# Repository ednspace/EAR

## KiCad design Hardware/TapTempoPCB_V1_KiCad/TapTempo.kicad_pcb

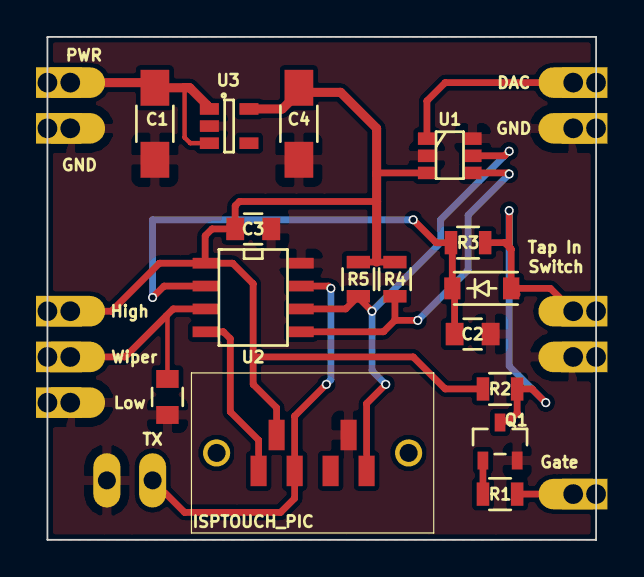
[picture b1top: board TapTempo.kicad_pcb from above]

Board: 2 copper layers, 30.5 x 27.9 mm, 27 parts (0 on the bottom side), 13 nets.

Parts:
C1, C4: 1uF; C_1206_HandSoldering
C2, C3, C5: .1uF; C_0805
D1: DIODE; SOD-123
J1: ISPTOUCH_PIC; ICSP_TOUCH_AVX_9188_6-WAY_MATING_GUIDE
P1: PWR; Castellation
P2, P11: GND; Castellation
P3: CONN_01X02; PINHEAD1-2
P4: DAC; Castellation
P5: Gate; Castellation
P6: Switch_1; Castellation
P7: Switch_2; Castellation
P8: High; Castellation
P9: Wiper; Castellation
P10: Low; Castellation
Q1: 2N3904; sot23
R1: 10K; R_0805
R2: 100K; R_0805
R3, R4, R5: 4.7K; R_0805
U1: MCP4725; SOT-23-6
U2: PIC12F1822; SOIC-8-W
U3: LDK220; SOT-23-5

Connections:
GND: C1.1, C2.2, C3.2, C4.1, C5.2, J1.6, P2.1, P3.1, P7.1, P10.1, P11.1, Q1.2, U1.2, U1.6, U2.8, U3.2
Gatein: P5.1, R1.1
MCLR: J1.1, U2.4
unnamed: C1.2, P1.1, U3.1, U3.3
unnamed: D1.1, P6.1, Q1.3, R2.2, R3.1
unnamed: P4.1, U1.1
unnamed: Q1.1, R1.2
PGC: J1.5, R5.1, U1.5, U2.6
PGD: J1.3, P3.2, U2.7
POT: C5.1, P9.1, U2.3
SDA: R4.2, U1.4, U2.5
TAP: C2.1, D1.2, R3.2, U2.2
VCC: C3.1, C4.2, J1.2, P8.1, R2.1, R4.1, R5.2, U1.3, U2.1, U3.5

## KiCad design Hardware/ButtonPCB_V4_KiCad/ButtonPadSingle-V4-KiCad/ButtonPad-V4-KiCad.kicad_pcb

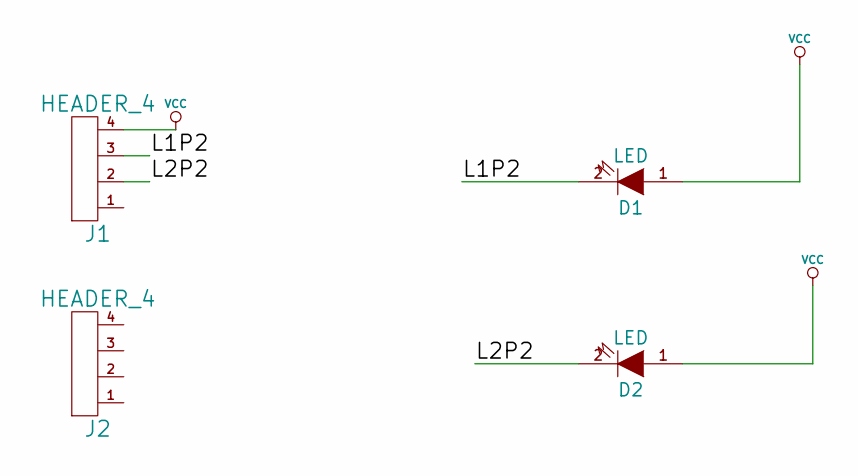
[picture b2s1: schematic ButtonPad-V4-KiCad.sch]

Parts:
D1, D2: LED
J1, J2: HEADER_4

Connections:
/L1P2: D1.2 (K), J1.3
/L2P2: D2.2 (K), J1.2
VCC: D1.1 (A), D2.1 (A), J1.4

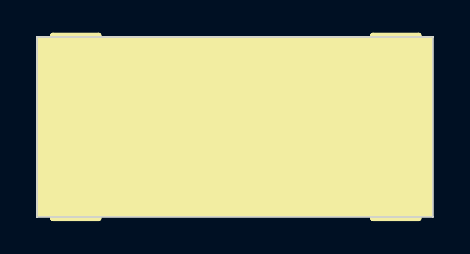
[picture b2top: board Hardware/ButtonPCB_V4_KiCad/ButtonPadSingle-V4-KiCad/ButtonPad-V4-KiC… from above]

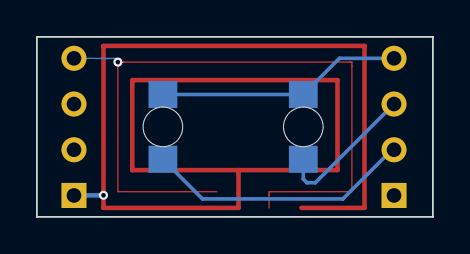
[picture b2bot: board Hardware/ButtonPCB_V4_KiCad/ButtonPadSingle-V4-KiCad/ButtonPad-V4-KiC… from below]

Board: 2 copper layers, 22.0 x 10.0 mm, 4 parts (2 on the bottom side), 3 nets.

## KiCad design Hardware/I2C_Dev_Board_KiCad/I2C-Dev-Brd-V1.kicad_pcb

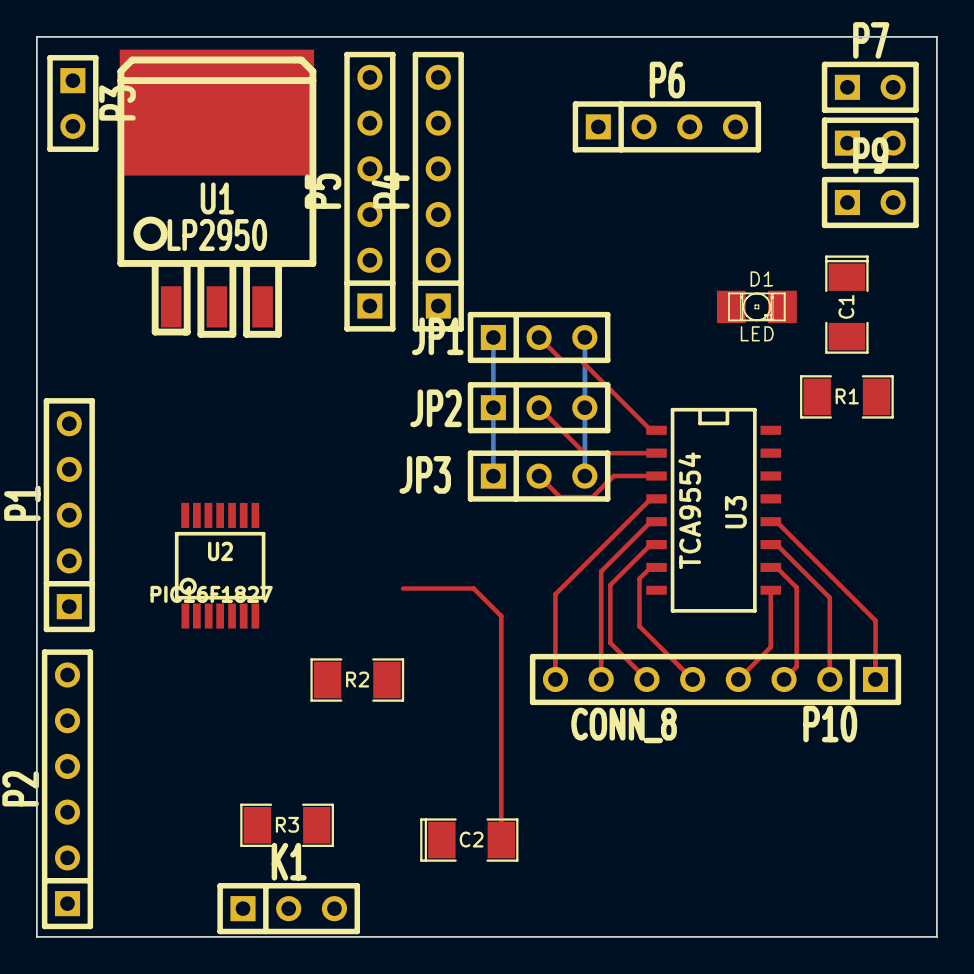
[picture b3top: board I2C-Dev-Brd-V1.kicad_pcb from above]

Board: 2 copper layers, 50.0 x 50.0 mm, 23 parts (0 on the bottom side), 26 nets.

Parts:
C1: 1uF; SM1206POL
C2: 4.7uF; SM1206POL
D1: LED; LED-1206
JP1, JP2, JP3: JUMPER3; SIL-3
K1: POTS; SIL-3
P1: PICKIT2; SIL-5
P2: FTDI SERIAL; SIL-6
P3, P7, P8, P9: CONN_2; SIL-2
P4, P5: CONN_6; SIL-6
P6: CONN_4; SIL-4
P10: CONN_8; SIL-8
R1: 330; SM1206
R2, R3: 4.7K; SM1206
U1: LP2950; TO263
U2: PIC16F1827; SSOP14
U3: TCA9554; SO16N

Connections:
+3.3V: C2.1, JP1.3, JP2.3, JP3.3, P4.1, P4.2, P4.3, P4.4, P4.5, P4.6, R2.1, R3.1, U1.1, U2.14, U3.16
/A0: JP1.2, U3.1
/A1: JP2.2, U3.2
/A2: JP3.2, U3.3
/BLINK: R1.1, U2.9
/I2C_CLK: P8.1, P9.1, R2.2, U2.10, U3.14
/I2C_DAT: P7.2, P8.2, P9.2, R3.2, U2.7, U3.15
/MCLR: P1.5, U2.4
/P0: P10.8, U3.4
/P1: P10.7, U3.5
/P2: P10.6, U3.6
/P3: P10.5, U3.7
/P4: P10.4, U3.9
/P5: P10.3, U3.10
/P6: P10.2, U3.11
/P7: P10.1, U3.12
/PGC: P1.1, U2.12
/PGD: P1.2, U2.13
/RXD: P2.5, U2.11
/TXD: P2.4, U2.8
GND: C1.2, C2.2, D1.2, JP1.1, JP2.1, JP3.1, P1.3, P2.1, P3.1, P5.1, P5.2, P5.3, P5.4, P5.5, P5.6, U1.2, U2.5, U3.8
unnamed: K1.3, U2.1
unnamed: K1.2, U2.2
unnamed: D1.1, R1.2
unnamed: K1.1, U2.3
VDD: C1.1, P1.4, P2.3, P3.2, U1.3

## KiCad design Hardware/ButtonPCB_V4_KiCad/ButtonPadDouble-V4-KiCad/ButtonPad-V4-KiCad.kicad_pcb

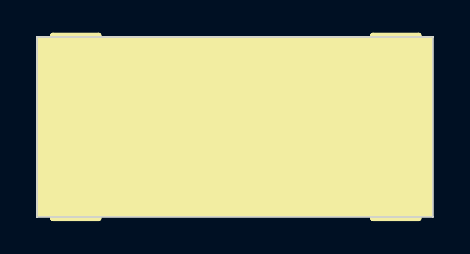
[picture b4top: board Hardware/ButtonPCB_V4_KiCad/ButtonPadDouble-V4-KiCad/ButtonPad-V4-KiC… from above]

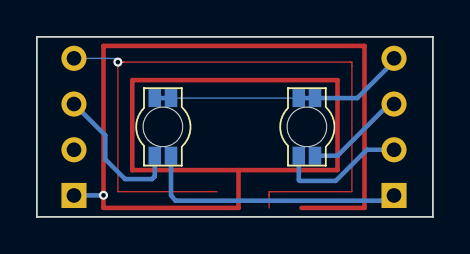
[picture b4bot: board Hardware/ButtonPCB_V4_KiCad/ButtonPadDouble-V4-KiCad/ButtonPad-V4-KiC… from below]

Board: 2 copper layers, 22.0 x 10.0 mm, 4 parts (2 on the bottom side), 5 nets.

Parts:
J1, J2: HEADER_4; SIL-4
LED1, LED2: BICOLORLED; BiColorLED

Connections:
/L1P1: J1.3, LED1.1
/L1P2: J1.2, LED1.2
/L2P1: J1.1, LED2.1
/L2P2: J2.3, LED2.2
VCC: J1.4, LED1.3, LED1.4, LED2.3, LED2.4

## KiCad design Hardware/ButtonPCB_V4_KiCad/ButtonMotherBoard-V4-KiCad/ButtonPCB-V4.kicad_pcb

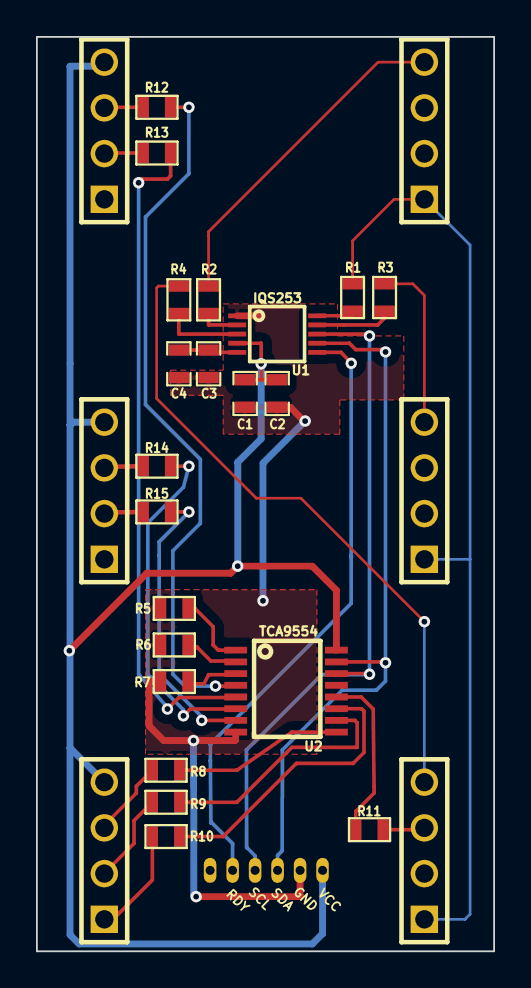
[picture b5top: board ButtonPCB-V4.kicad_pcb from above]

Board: 2 copper layers, 25.4 x 50.8 mm, 28 parts (1 on the bottom side), 33 nets.

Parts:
C1: 100pF; SM0603_Capa
C2, C4: 100uF; SM0603_Capa
C3: 10pF; SM0603_Capa
P1, P2, P3, P4, P5, P6: CONN_4; PIN_ARRAY_4x1
P7: JST-PH6; con-molex-53048-06
R1, R2, R3, R4: 470; SM0603
R5, R6, R7: 4.7k; SM0603
R8, R9, R10, R11, R12, R13, R14, R15: R; SM0603
U1: IQS253; MSOP10-0.5
U2: TCA9554; TSSOP16

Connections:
/Button1LED1: P1.3, R12.1
/Button1LED2: P1.2, R13.1
/Button2LED1: P3.3, R14.1
/Button2LED2: P3.2, R15.1
/Button3LED1: P5.3, R8.1
/Button3LED2: P5.2, R9.1
/Button3LED3: P5.1, R10.1
/Button3LED4: P6.3, R11.1
/CTX: P2.1, P4.1, P6.1, R1.1
/CX0: P2.4, R2.2
/CX1: P6.4, R4.2
/CX2: P4.4, R3.1
/RDY/ND: P7.5, U1.6
/SCL: P7.4, U1.8, U2.14
/SDA: P7.3, U1.7, U2.15
GND: C1.2, C2.2, C3.2, C4.2, P7.2, R5.1, R6.1, R7.1, U1.1, U2.8
unnamed: C3.1, C4.1, U1.5
unnamed: R1.2, U1.10
unnamed: R2.1, U1.2
unnamed: R3.2, U1.9
unnamed: R4.1, U1.3
unnamed: R5.2, U2.1
unnamed: R6.2, U2.2
unnamed: R7.2, U2.3
unnamed: R8.2, U2.9
unnamed: R9.2, U2.10
unnamed: R10.2, U2.11
unnamed: R11.2, U2.12
unnamed: R12.2, U2.4
unnamed: R13.2, U2.5
unnamed: R14.2, U2.6
unnamed: R15.2, U2.7
VCC: C1.1, C2.1, P1.4, P3.4, P5.4, P7.1, U1.4, U2.16

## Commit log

2014-11-06 Drawing the TapTempo schematic adding the first of the components
2014-11-07 Added the DAC and cleaned up the schematic a little bit.
2014-11-12 Anotation of schematic plus initial parts selection
2014-11-13 still organizing
2015-02-12 Added LUT table to firmware for VCO also added spreadsheet for LUT
2015-06-20 Lots of changes to the TapTempo Board, made it all consistantly surface mount, turned into a module and created gerbers.
2015-09-22 Pushing latest schematic brd file and some 12F1822 tests
2015-09-22 Pushing all updates mostly code tests and some TT board changes
2015-10-08 Updating codebase with delivered code that is AWESOME and TEENSYLC test code plus new spreadsheets for error calculation...
2016-07-22 Updating TapTempo.pro
